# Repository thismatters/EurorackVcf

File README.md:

# Voltage Controlled Filter

The Voltage Controlled Filter (VCF) filters incoming audio signals to the degree specified by the control voltages. This implementation uses a transistor ladder similar to that found in Moog synthesizers with both a cutoff frequency and a resonator control.

The circuit here is based on the [MiniMoog VCF](https://yusynth.net/Modular/EN/MOOGVCF/index.html) with minor tweaks to make it more Eurorack friendly. The changes I've made are thus:
* Selected resistors appropriate for +/-12V rails,
* Added polarity protection so that a backward power header doesn't fry anything (twin series schotty diodes: BAT54SL),
* Selected a modern dual NPN diode package for matched transistors,
* Full surface mount design.

The Yusynth page is a treasure trove of information about this circuit that I am too amateur to claim as my own; please read that outstanding page before using this circuit. The page provides many details and other implementations of this circuit that you may find suitable.

The KiCAD project here uses the library/footprints [found in my companion repo](https://github.com/thismatters/EurorackKiCAD).

## Width

8hp on a standard 3U rack.

## Inputs

Potentiometer labeled `cutoff` controls the cutoff frequency, which is also augmented by the `cv1` input and potentiometer. Two other CV inputs `cv2` and `cv3` combine with `cv1` and the `cutoff` knob to set the frequency. An additional potentiometer for setting the `emph`asis. Two audio signal inputs, `in1` and `in2` are adjusted for level by twin potentiometers and combine as the audio input to the filter.

## Output

A single output labeled `out` yields the filtered audio signal.

## Adjustment

### Volt per Octave tracking

1. Set the `cutoff` knob to its minimum setting (counterclockwise).
1. Set the `emph` knob to its minimum setting (counterclockwise).
1. Apply 0V to `cv2`.
1. Measure 0mV at the test point `TP1`.
1. Apply 1V to `cv2`.
1. Adjust RV6 to measure 18.2mV at `TP1`.
1. Apply 5V to `cv2`.
1. Adjust RV6 to measure 91mV at `TP1`.
1. Set the `emph` knob to its maximum setting (auto oscillation).
1. Connect a keyboard to `cv2` and play a scale.
1. Adjust RV6 to achieve good chromatic tracking.

### Frequency Range

1. Apply a 32Hz sine wave to `in1`.
1. Set the `emph` knob to its minimum setting.
1. Set the `cutoff` knob to its minimum setting.
1. Adjust RV7 until the 32Hz tone is muted.

### Emphasis

1. Adjust RV8 in order to reach auto-oscillation near 95% of the full range of the `emph` potentiometer.

## Vendors

There are part numbers in the [BOM](moog-vcf.csv) for many of the parts (not for basic passives though) at the following vendors:

* [Mouser](https://www.mouser.com): Needs no introduction. Get your ICs from here (or [digikey](https://www.digikey.com)).
* [Tayda Electronics](https://www.taydaelectronics.com/): Good supplier for passive components; audio jacks, and potentiometers. Their audio jacks are slightly smaller than the thonkiconn from thonk.
* [Love My Switches](https://lovemyswitches.com/): Has [really good knobs](https://lovemyswitches.com/anodized-aluminum-knob-the-lo-fi-1-4-smooth-shaft-12-5mm-od/) to go on those potentiometers!
* [OSHPark](https://oshpark.com/): Fast and (relatively) cheap PCB manufacturer. The [V0 Circuit](https://oshpark.com/shared_projects/SO7swty4) works pretty well.

## Known Bugs

### v0

* Vias on Q5 (B1 and B2) block pads. (doesn't prohibit function)
* C8 hole pitch too narrow (should be 3mm)

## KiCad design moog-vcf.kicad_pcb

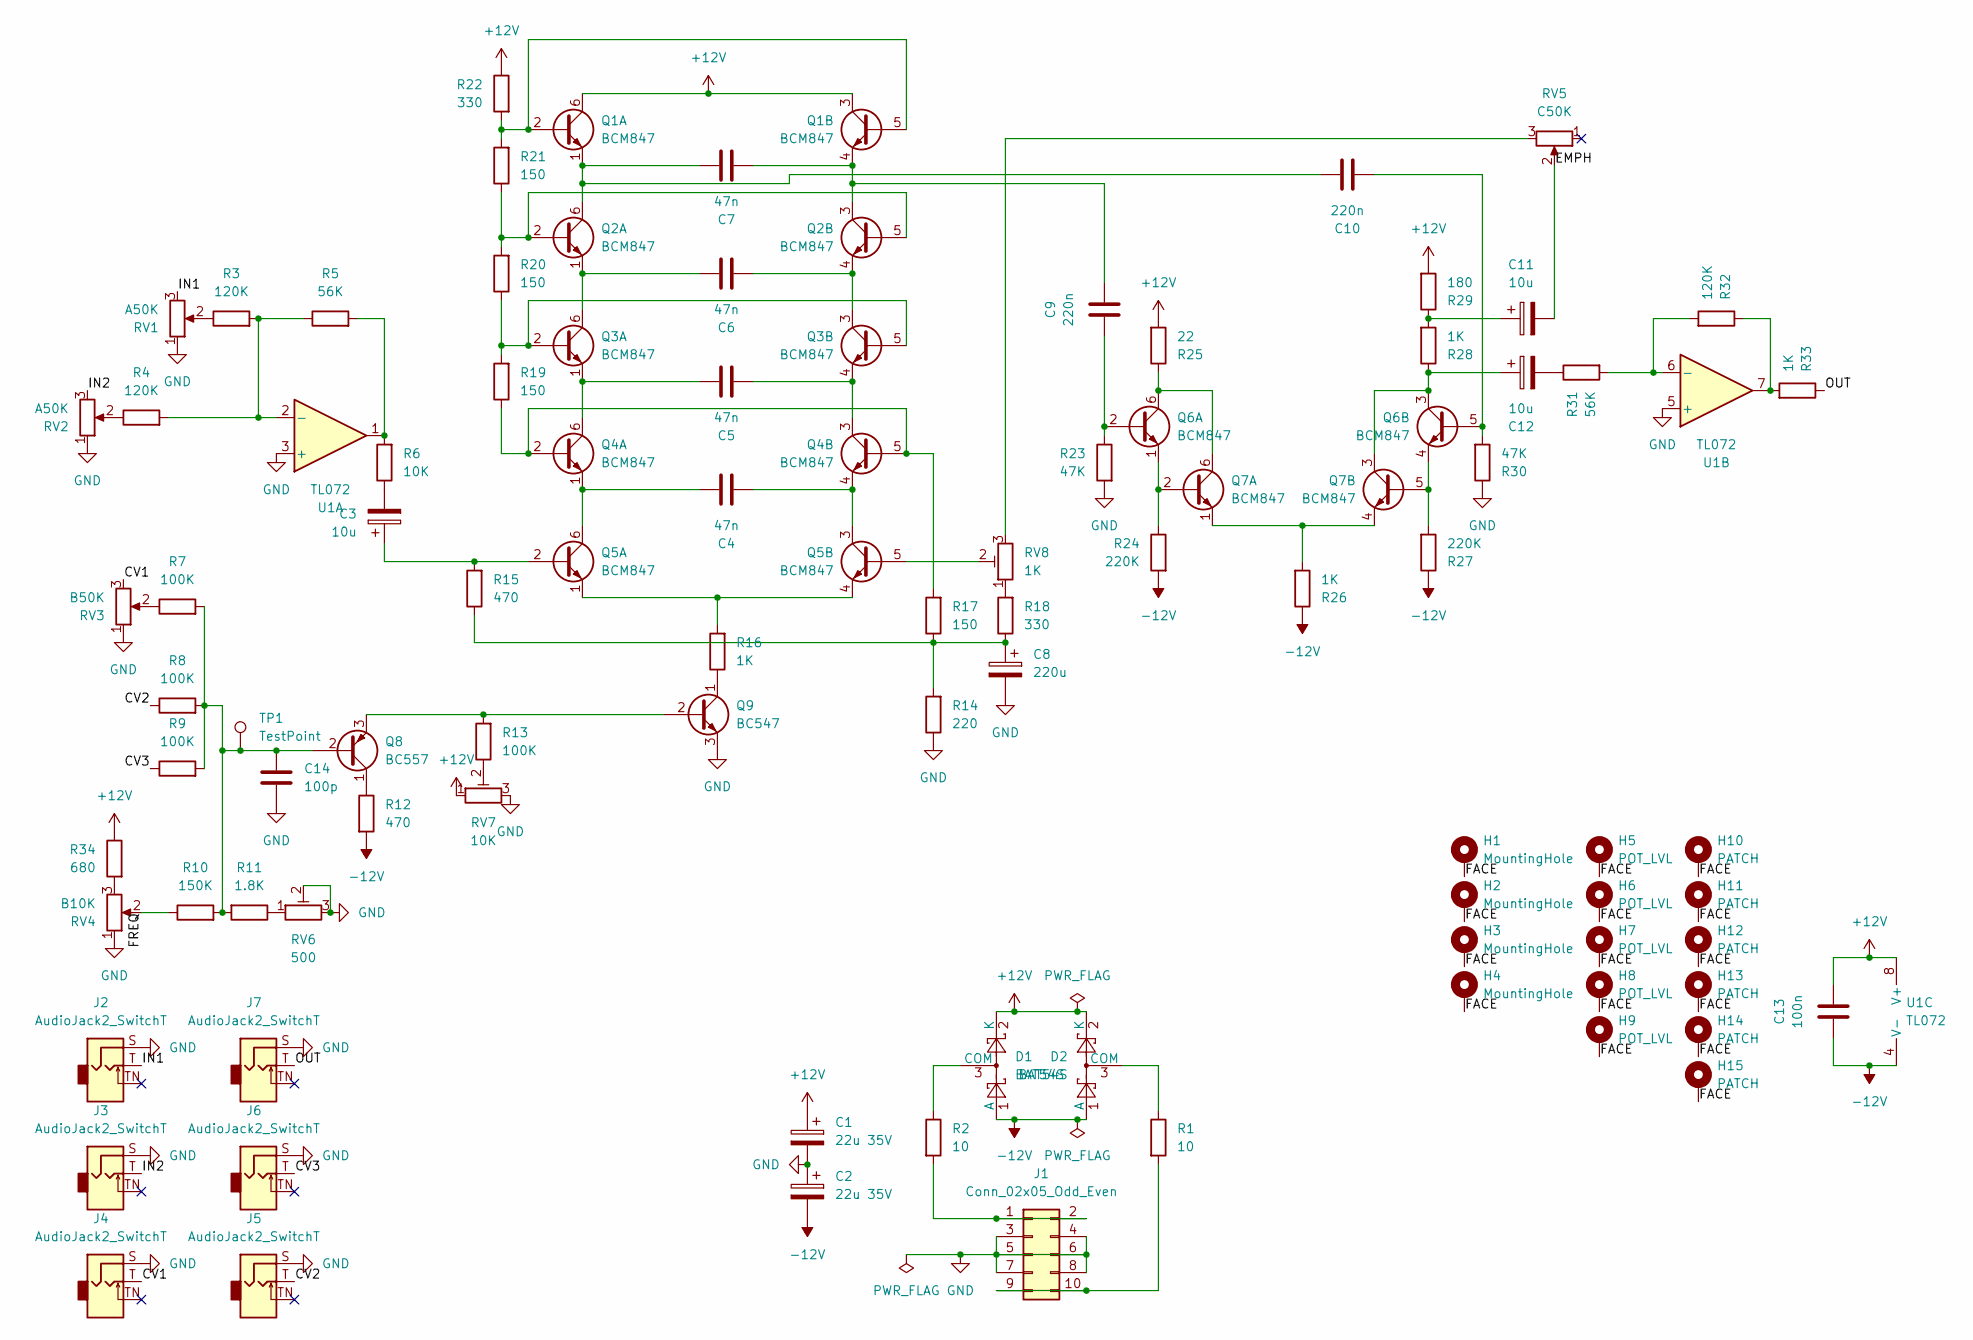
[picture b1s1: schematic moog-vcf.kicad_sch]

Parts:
C1, C2: 22u 35V; CP_Radial_D5.0mm_P2.50mm
C3, C11, C12: 10u; CP_Radial_D5.0mm_P2.50mm
C4, C5, C6, C7: 47n; C_0805_2012Metric
C8: 220u; CP_Radial_D8.0mm_P2.50mm
C9, C10: 220n; C_0805_2012Metric
C13: 100n; C_0805_2012Metric
C14: 100p; C_0805_2012Metric
D1, D2: BAT54S; SOT-23; PartNum 863-BAT54SLT1G
H1, H2, H3, H4: MountingHole; Mech-MountingHole
H5, H6, H7, H8, H9: POT_LVL; Mech-Potentiometer-Hole_level
H10, H11, H12, H13, H14: PATCH; Mech-AudioJack-Hole
H15: PATCH; Mech-AudioJack-Hole-Output
J1: Conn_02x05_Odd_Even; PinHeader_2x05_P2.54mm_Vertical; PartNum A-2939
J2, J3, J4, J5, J6, J7: AudioJack2_SwitchT; AudioJack2_Tayda_A-2566; PartNum A-2566
Q1, Q2, Q3, Q4, Q5, Q6, Q7: BCM847; TSOP-6_1.65x3.05mm_P0.95mm; PartNum 771-BCM847DS135
Q8: BC557; TO-92L_Inline_Wide; PartNum 637-BC557B
Q9: BC547; TO-92L_Inline_Wide; PartNum 637-BC547C
R1, R2: 10; R_0805_2012Metric
R3, R4, R32: 120K; R_0805_2012Metric
R5, R31: 56K; R_0805_2012Metric
R6: 10K; R_0805_2012Metric
R7, R8, R9, R13: 100K; R_0805_2012Metric
R10: 150K; R_0805_2012Metric
R11: 1.8K; R_0805_2012Metric
R12, R15: 470; R_0805_2012Metric
R14: 220; R_0805_2012Metric
R16, R26, R28, R33: 1K; R_0805_2012Metric
R17, R19, R20, R21: 150; R_0805_2012Metric
R18, R22: 330; R_0805_2012Metric
R23, R30: 47K; R_0805_2012Metric
R24, R27: 220K; R_0805_2012Metric
R25: 22; R_0805_2012Metric
R29: 180; R_0805_2012Metric
R34: 680; R_0805_2012Metric
RV1, RV2: A50K; Potentiometer_RV16AF-41-15R1; PartNum A-4182
RV3: B50K; Potentiometer_RV16AF-41-15R1; PartNum A-2393
RV4: B10K; Potentiometer_RV16AF-41-15R1; PartNum A-2969
RV5: C50K; Potentiometer_RV16AF-41-15R1; PartNum A-4181
RV6: 500; Potentiometer_Bourns_3296W_Vertical
RV7: 10K; Potentiometer_Bourns_3296W_Vertical
RV8: 1K; Potentiometer_Bourns_3296W_Vertical
TP1: TestPoint; TestPoint_THTPad_D2.0mm_Drill1.0mm
U1: TL072; SOIC-8_3.9x4.9mm_P1.27mm; PartNum 595-TL072CDR

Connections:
+12V: C1.1, C13.1, D1.2 (K), D2.2 (K), Q1.3 (C2), Q1.6 (C1), R22.1, R25.2, R29.2, R34.1, RV7.1, U1.8 (V+)
-12V: C2.2, C13.2, D1.1 (A), D2.1 (A), R12.2, R24.2, R26.1, R27.1, U1.4 (V-)
/CV1: J4.T, RV3.3
/CV2: J5.T, R8.1
/CV3: J6.T, R9.1
/EMPH: C11.2, RV5.2
/FACE: H1.1, H2.1, H3.1, H4.1, H5.1, H6.1, H7.1, H8.1, H9.1, H10.1, H11.1, H12.1, H13.1, H14.1, H15.1
/FREQ: R10.1, RV4.2
/IN1: J2.T, RV1.3
/IN2: J3.T, RV2.3
/OUT: J7.T, R33.1
GND: C1.2, C2.1, C8.2, C14.2, J1.3, J1.4, J1.5, J1.6, J1.7, J1.8, J2.S, J3.S, J4.S, J5.S, J6.S, J7.S, Q9.3 (E), R14.1, R23.2, R30.1, RV1.1, RV2.1, RV3.1, RV4.1, RV6.2, RV6.3, RV7.3, U1.3 (+), U1.5 (+)
unnamed: C3.2, R6.1
unnamed: C8.1, R14.2, R15.1, R17.1, R18.1
unnamed: C11.1, R28.2, R29.1
unnamed: C12.2, R31.1
unnamed: D1.3 (COM), R2.1
unnamed: D2.3 (COM), R1.1
unnamed: J1.1, J1.2, R2.2
unnamed: J1.9, J1.10, R1.2
unnamed: Q1.2 (B1), Q1.5 (B2), R21.2, R22.2
unnamed: C7.1, C10.1, Q1.1 (E1), Q2.6 (C1)
unnamed: C7.2, C9.1, Q1.4 (E2), Q2.3 (C2)
unnamed: Q2.2 (B1), Q2.5 (B2), R20.2, R21.1
unnamed: C6.1, Q2.1 (E1), Q3.6 (C1)
unnamed: C6.2, Q2.4 (E2), Q3.3 (C2)
unnamed: Q3.2 (B1), Q3.5 (B2), R19.2, R20.1
unnamed: C5.1, Q3.1 (E1), Q4.6 (C1)
unnamed: C5.2, Q3.4 (E2), Q4.3 (C2)
unnamed: Q4.2 (B1), Q4.5 (B2), R17.2, R19.1
unnamed: C4.1, Q4.1 (E1), Q5.6 (C1)
unnamed: C4.2, Q4.4 (E2), Q5.3 (C2)
unnamed: C3.1, Q5.2 (B1), R15.2
unnamed: Q5.1 (E1), Q5.4 (E2), R16.2
unnamed: Q5.5 (B2), RV8.2
unnamed: C9.2, Q6.2 (B1), R23.1
unnamed: Q6.6 (C1), Q7.6 (C1), R25.1
unnamed: Q6.1 (E1), Q7.2 (B1), R24.1
unnamed: C10.2, Q6.5 (B2), R30.2
unnamed: C12.1, Q6.3 (C2), Q7.3 (C2), R28.1
unnamed: Q6.4 (E2), Q7.5 (B2), R27.2
unnamed: Q7.1 (E1), Q7.4 (E2), R26.2
unnamed: C14.1, Q8.2 (B), R7.2, R8.2, R9.2, R10.2, R11.2, TP1.1
unnamed: Q8.1 (C), R12.1
unnamed: Q8.3 (E), Q9.2 (B), R13.2
unnamed: Q9.1 (C), R16.1
unnamed: R3.1, RV1.2
unnamed: R4.1, RV2.2
unnamed: R5.2, R6.2, U1.1
unnamed: R7.1, RV3.2
unnamed: R11.1, RV6.1
unnamed: R13.1, RV7.2
unnamed: R18.2, RV8.1
unnamed: R32.1, R33.2, U1.7
unnamed: R34.2, RV4.3
unnamed: RV5.3, RV8.3
unnamed: R3.2, R4.2, R5.1, U1.2 (-)
unnamed: R31.2, R32.2, U1.6 (-)

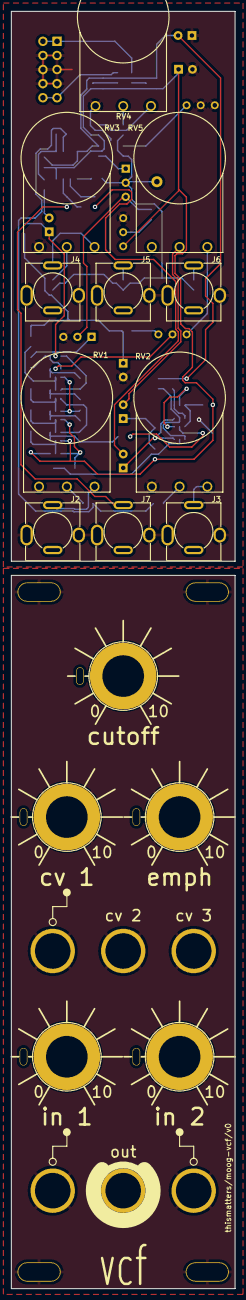
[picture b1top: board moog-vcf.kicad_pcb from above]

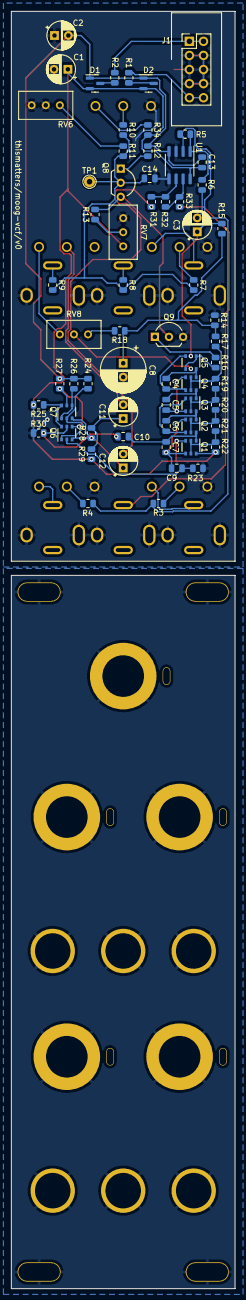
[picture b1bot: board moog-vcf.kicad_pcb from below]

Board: 2 copper layers, 40.3 x 230.1 mm, 91 parts (65 on the bottom side), 58 nets.

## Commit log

2024-07-07 adding readme
2024-08-11 adding known bugs from prototype build
2024-11-25 adding pcb to readme
2025-01-12 adding schematic
